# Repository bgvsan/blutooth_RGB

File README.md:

Bluetooth RGB Module
============

This is an HC-06 bluetooth / pic module for drive an rgb led throught your modile phone

Protocol
============
Read from serial port the Red/Green/Blue value a and set the pwm output to show the correct color
Package send
{0x01,HEXRed,HEXGreen;HEXBlue,0xFF}

Implemented
============
- Board and gerber file (powered by USB 5V Tollerant)
- Comunication protocol
- Bluetooth library
- WP8 Application

Module Pic12f1572
============

Video
============

Still to implement
============
- CRC
- Response / re-Transmit ACK

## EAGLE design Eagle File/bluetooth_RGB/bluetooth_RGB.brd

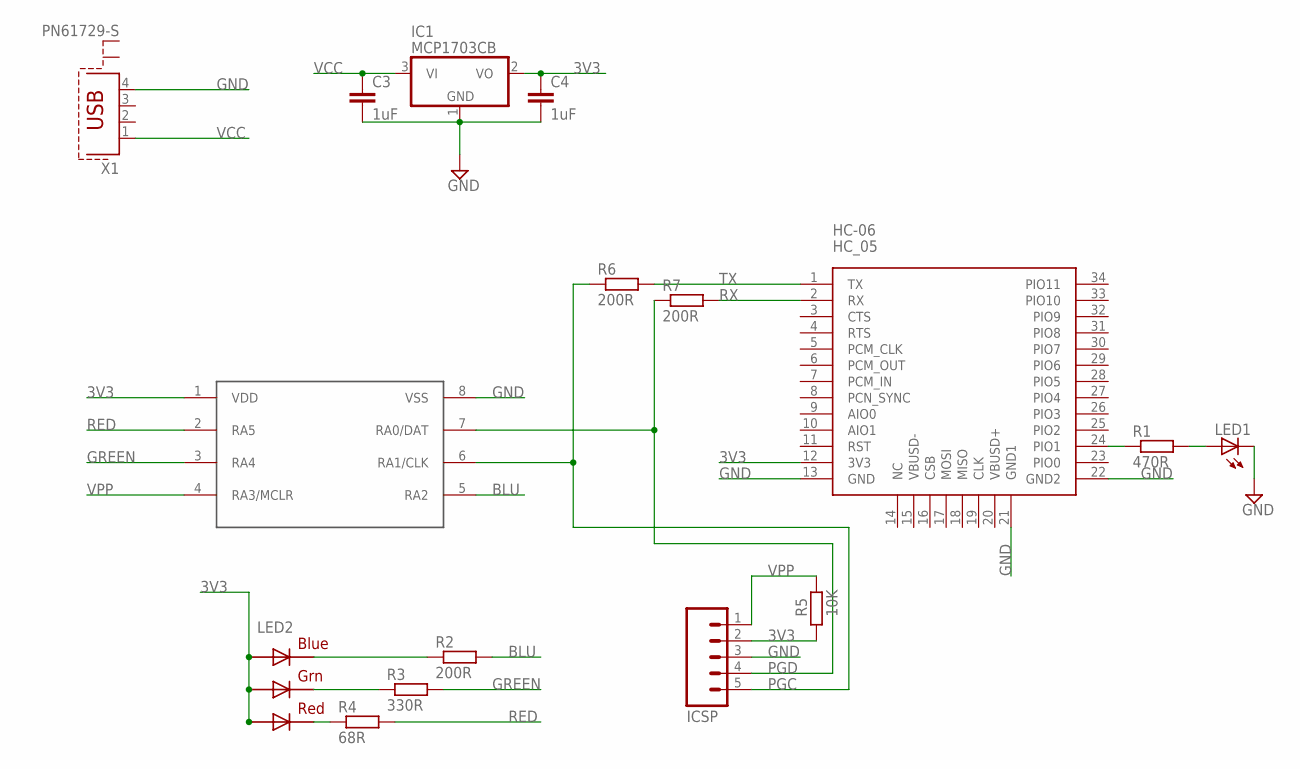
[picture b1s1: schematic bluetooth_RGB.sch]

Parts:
C3, C4: 1uF; 0805
HC-06: HC_05; BLUETOOTH_SMD
IC1: MCP1703CB; SOT23
ICSP: M05PTH; 1X05
LED1: LEDCHIPLED_0805; CHIPLED_0805
LED2: RGBLED5050
R1: 470R; M0805
R2: 200R; M0805
R3: 330R; M0805
R4: 68R; M0805
R5: 10K; M0805
R6, R7: 200R; R0805
U2: PIC12F1572; MSOP8
X1: PN61729-S

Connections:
3V3: C4.1, HC-06.12 (3V3), IC1.2 (VO), ICSP.2, LED2.1 (GREEN_A), LED2.2 (RED_A), LED2.3 (BLUE_A), R5.1, U2.1 (VDD)
BLU: R2.2, U2.5 (RA2)
GND: C3.2, C4.2, HC-06.13 (GND), HC-06.21 (GND1), HC-06.22 (GND2), IC1.1 (GND), ICSP.3, LED1.C, U2.8 (VSS), X1.4
GREEN: R3.2, U2.3 (RA4)
unnamed: LED2.4 (BLUE_C), R2.1
unnamed: LED1.A, R1.2
unnamed: HC-06.24 (PIO1), R1.1
unnamed: LED2.6 (GREEN_C), R3.1
unnamed: LED2.5 (RED_C), R4.1
PGC: ICSP.5, R6.1, U2.6 (RA1/CLK)
PGD: ICSP.4, R7.1, U2.7 (RA0/DAT)
RED: R4.2, U2.2 (RA5)
RX: HC-06.2 (RX), R7.2
TX: HC-06.1 (TX), R6.2
VCC: C3.1, IC1.3 (VI), X1.1
VPP: ICSP.1, R5.2, U2.4 (RA3/MCLR)

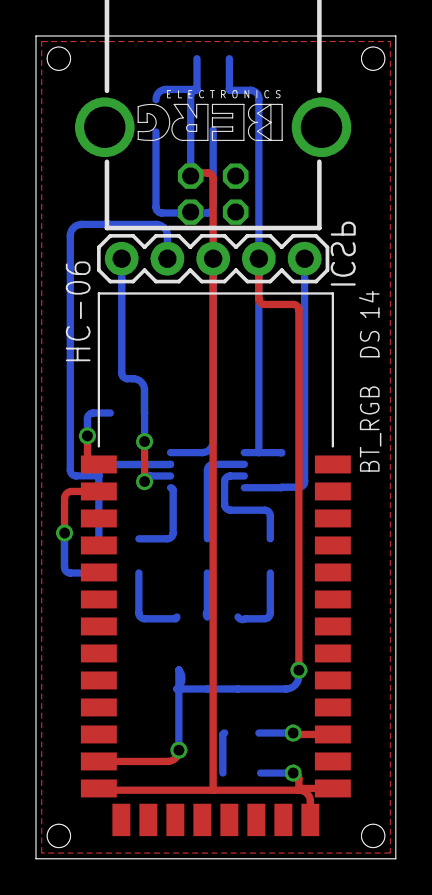
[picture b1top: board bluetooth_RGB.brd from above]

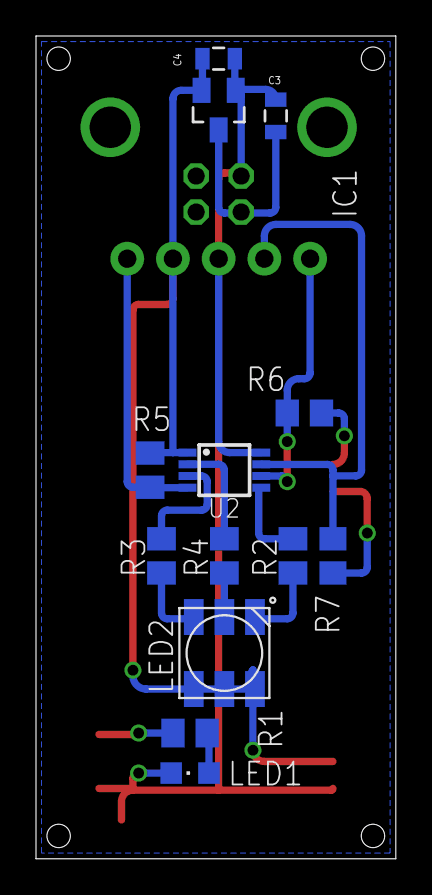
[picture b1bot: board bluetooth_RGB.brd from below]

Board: 2 copper layers, 20.0 x 45.7 mm, 16 parts (13 on the bottom side), 16 nets.

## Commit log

2014-06-06 readme summary
2014-06-06 first app xaml and button
2014-06-07 read and write address to isolate storage and send
2014-06-08 First Step
    Usart read and pic config (init and pin)
2014-06-09 Read Me update
2014-08-03 first working commit
2014-08-03 Code clean up
2014-08-04 Eagle file
2014-09-07 stuff from project
2014-09-07 Revision app
2014-09-07 readme Update
2014-09-07 readme update video
2014-09-07 Add Photo Hardware
2014-09-07 add relative image
2014-09-07 image resized
2014-12-07 add microchip library

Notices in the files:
parts and their libraries:
SparkFun-Passives: Licensing: CC v3.0 Share-Alike You are welcome to use this library for commercial purposes.
